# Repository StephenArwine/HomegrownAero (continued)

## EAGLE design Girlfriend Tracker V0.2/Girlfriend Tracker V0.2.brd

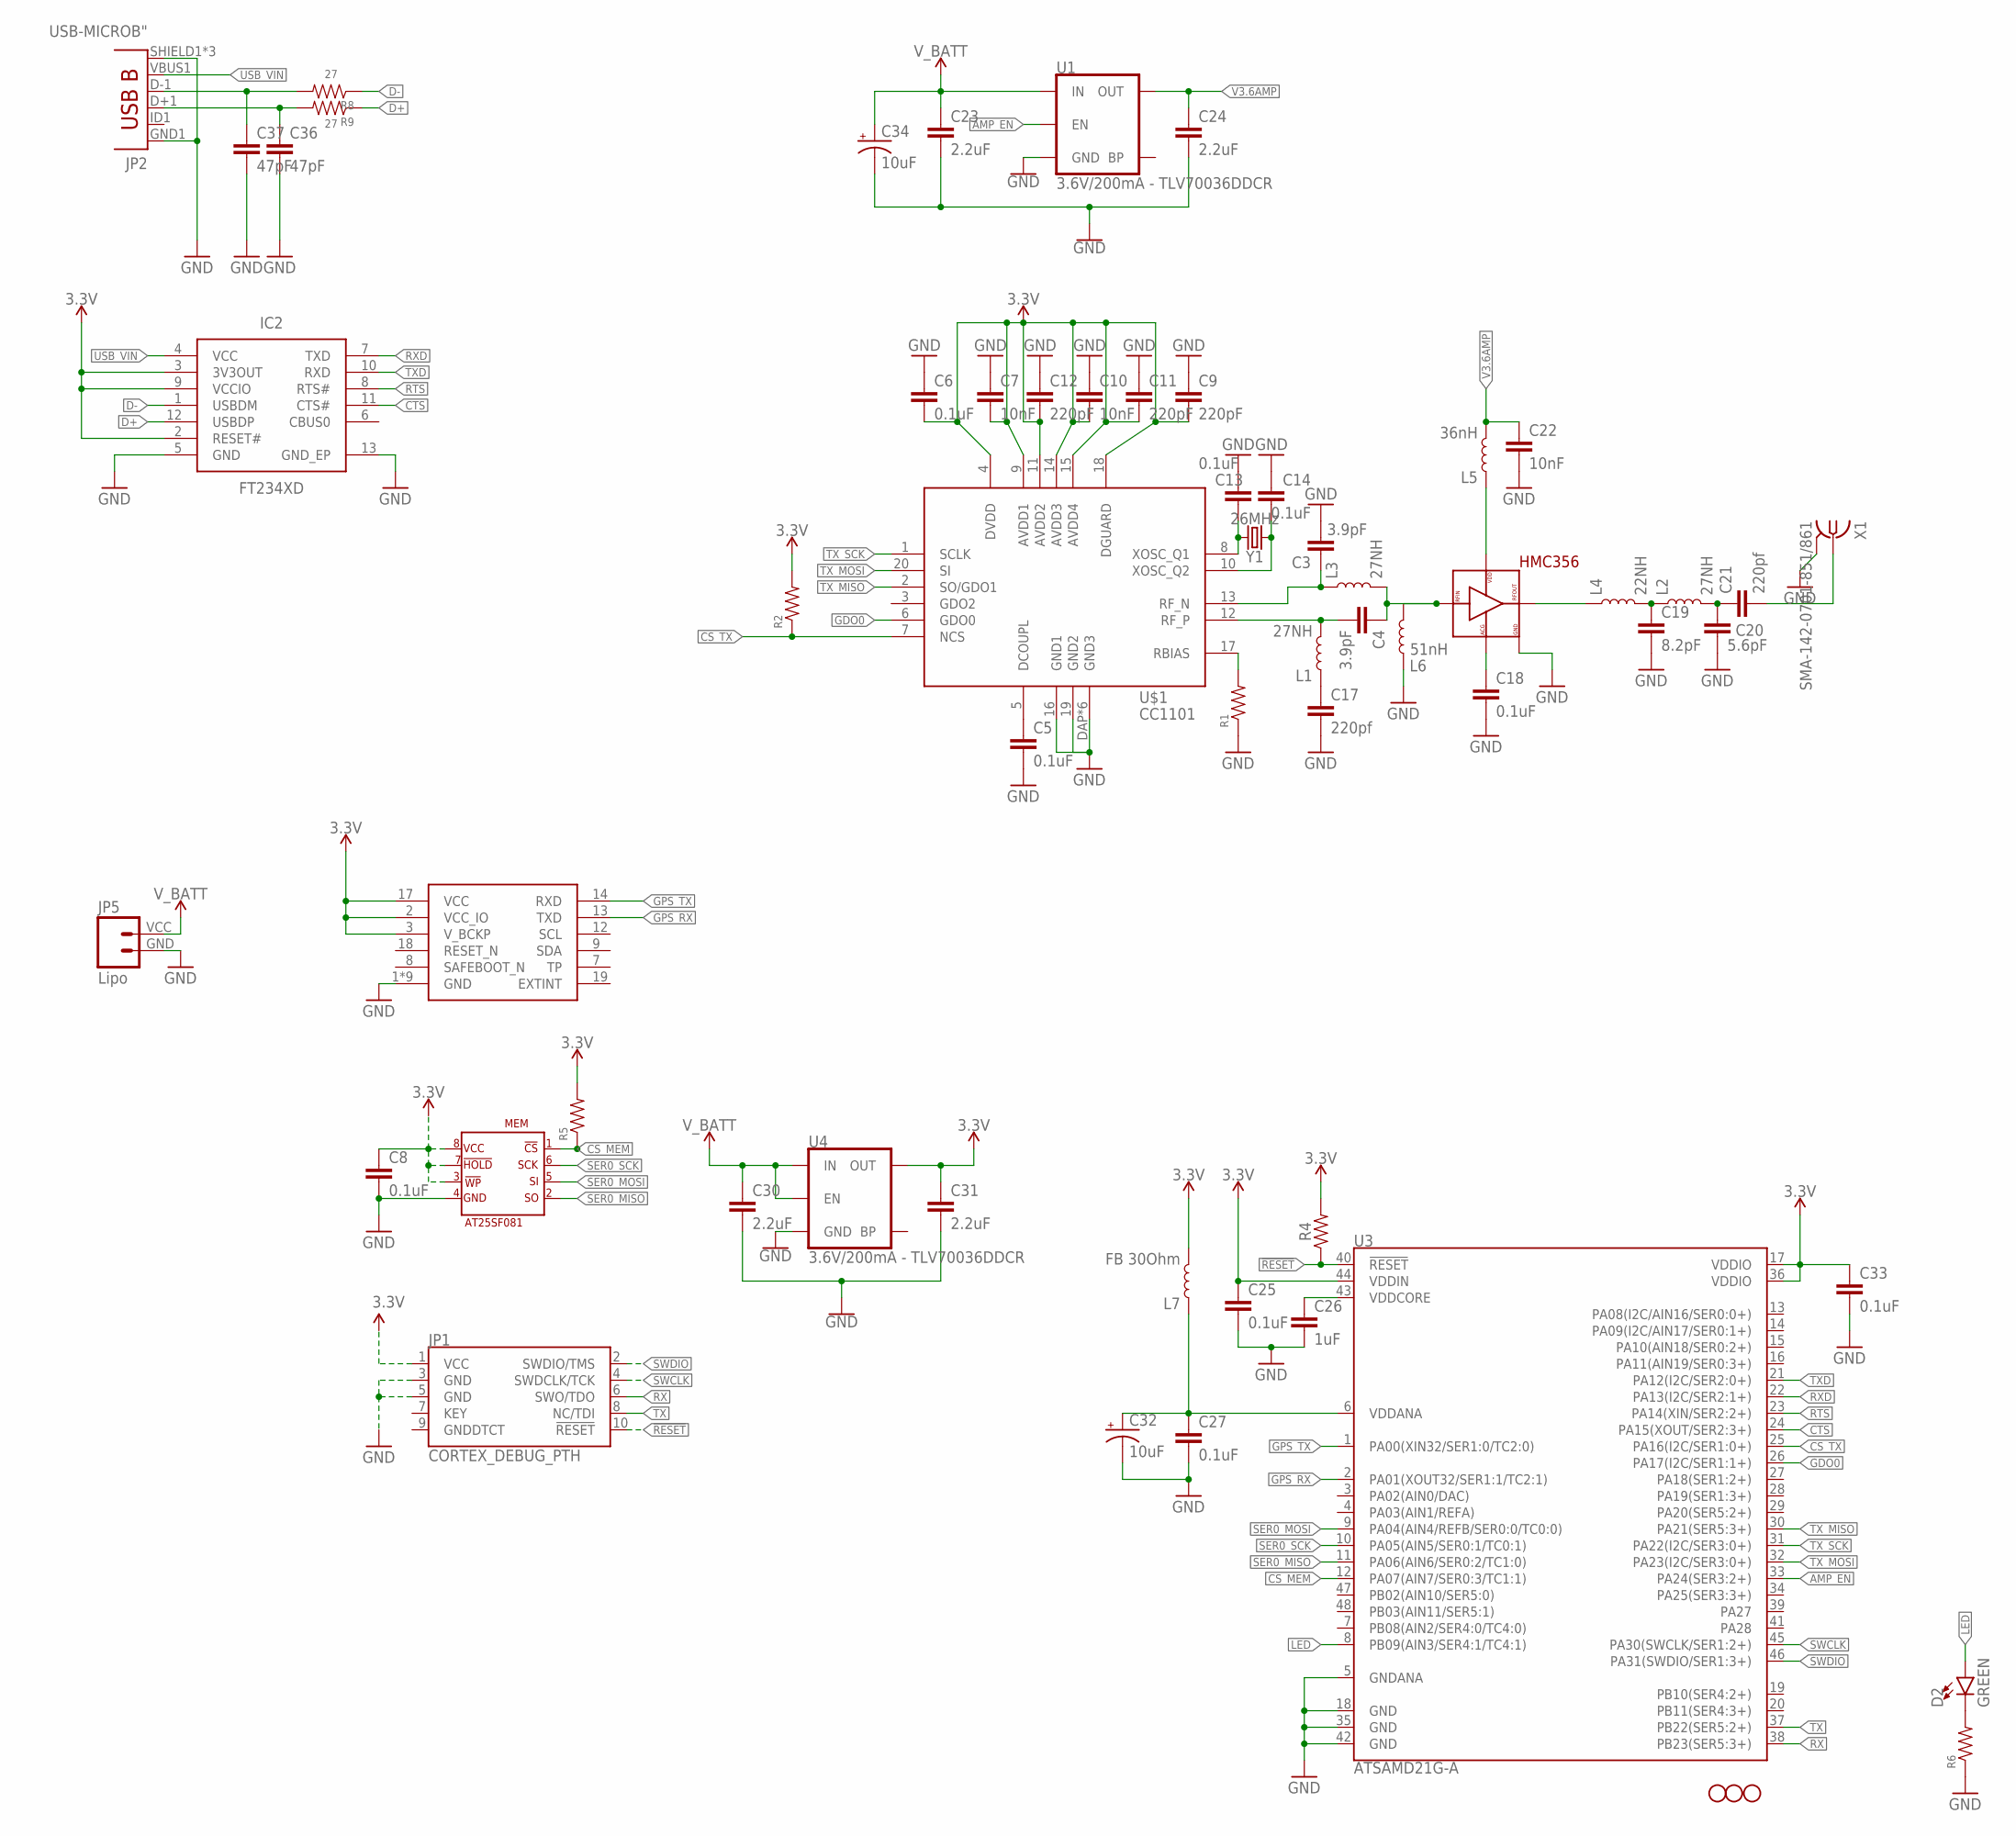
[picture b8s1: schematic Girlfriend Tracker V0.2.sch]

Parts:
C3, C4: 3.9pF; 0402
C5, C6, C8, C13, C14, C18, C25, C27, C33: 0.1uF; 0402
C7, C10, C22: 10nF; 0402
C9, C11, C12: 220pF; 0402
C17, C21: 220pf; 0402
C19: 8.2pF; 0402
C20: 5.6pF; 0402
C23, C24, C30, C31: 2.2uF; 0603
C26: 1uF; 0402
C32, C34: 10uF; EIA3216
C36, C37: 47pF; 0402
D2: GREEN; LED-1206
H1, H2, H3: STAND-OFFTIGHT; STAND-OFF-TIGHT
IC1: SAM-M8Q
IC2: FT234XD; SON45P300X300X80-13N
JP1: CORTEX_DEBUG_PTH; 2X5-PTH-1.27MM
JP2: USB-MICROB"; USB-B-MICRO-SMD_V03
JP5: Lipo; JST-2-SMD-VERT
L1, L2, L3: 27NH; 0402
L4: 22NH; 0402
L5: 36nH; 0402
L6: 51nH; 0402
L7: FB 30Ohm; 0603
MEM: AT25SF081
R1, R2, R4, R5, R6: 0402
R8, R9: 27; 0402
U1, U4: 3.6V/200mA - TLV70036DDCR; SOT23-5
U3: ATSAMD21G-A; TQFP-48
U$1: CC1101
U$3: HMC356; QFN16_HMC356
X1: SMA-142-0701-851/861; J502-ND-142-0701-851/861
Y1: 26MHz; CRYSTAL-SMD-3.2X2.5MM

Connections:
3.3V: C6.2, C7.2, C8.1, C9.2, C10.2, C11.2, C12.2, C25.1, C31.1, C33.1, IC1.2 (VCC_IO), IC1.3 (V_BCKP), IC1.17 (VCC), IC2.2 (RESET#), IC2.3 (3V3OUT), IC2.9 (VCCIO), JP1.1 (VCC), L7.2, MEM.!HOLD, MEM.!WP, MEM.VCC, R2.2, R4.2, R5.2, U3.17 (VDDIO), U3.36 (VDDIO), U3.44 (VDDIN), U4.5 (OUT), U$1.4 (DVDD), U$1.9 (AVDD1), U$1.11 (AVDD2), U$1.14 (AVDD3), U$1.15 (AVDD4), U$1.18 (DGUARD)
!RESET: JP1.10 (!RESET), R4.1, U3.40 (!RESET!)
AMP_EN: U1.3 (EN), U3.33 (PA24(SER3:2+))
CS_MEM: MEM.!CS, R5.1, U3.12 (PA07(AIN7/SER0:3/TC1:1))
CS_TX: R2.1, U3.25 (PA16(I2C/SER1:0+)), U$1.7 (NCS)
CTS: IC2.11 (CTS#), U3.24 (PA15(XOUT/SER2:3+))
D+: IC2.12 (USBDP), R9.1
D-: IC2.1 (USBDM), R8.1
GDO0: U3.26 (PA17(I2C/SER1:1+)), U$1.6 (GDO0)
GND: C3.2, C5.2, C6.1, C7.1, C8.2, C9.1, C10.1, C11.1, C12.1, C13.1, C14.2, C17.2, C18.2, C19.2, C20.2, C22.2, C23.2, C24.2, C25.2, C26.2, C27.2, C30.2, C31.2, C32.C (-), C33.2, C34.C (-), C36.2, C37.2, IC1.1 (GND), IC1.4 (GND), IC1.5 (GND), IC1.6 (GND), IC1.10 (GND), IC1.11 (GND), IC1.15 (GND), IC1.16 (GND), IC1.20 (GND), IC2.5 (GND), IC2.13 (GND_EP), JP1.3 (GND), JP1.5 (GND), JP2.GND1 (GND), JP2.SHIELD1 (SHIELD), JP2.SHIELD2 (SHIELD), JP2.SHIELD3 (SHIELD), JP5.GND (1), L6.1, MEM.GND, R1.1, R6.1, U1.2 (GND), U3.5 (GNDANA), U3.18 (GND), U3.35 (GND), U3.42 (GND), U4.2 (GND), U$1.16 (GND1), U$1.19 (GND2), U$1.DAP (GND3), U$1.P$1 (GND3), U$1.P$2 (GND3), U$1.P$3 (GND3), U$1.P$4 (GND3), U$1.P$5 (GND3), U$3.P$2, U$3.P$4, U$3.P$6, U$3.P$16, U$3.P$17, U$3.P$17_1, U$3.P$17_2, U$3.P$17_3, U$3.P$17_4, X1.G@1 (2), X1.G@2 (2), X1.G@3 (2), X1.G@4 (2)
GPS_RX: IC1.13 (TXD), U3.2 (PA01(XOUT32/SER1:1/TC2:1))
GPS_TX: IC1.14 (RXD), U3.1 (PA00(XIN32/SER1:0/TC2:0))
LED: D2.A, U3.8 (PB09(AIN3/SER4:1/TC4:1))
unnamed: C17.1, L1.1
unnamed: C36.1, JP2.D+1 (D+), R9.2
unnamed: C19.1, L2.1, L4.2
unnamed: C13.2, U$1.8 (XOSC_Q1), Y1.3 (2)
unnamed: C20.1, C21.1, L2.2
unnamed: C5.1, U$1.5 (DCOUPL)
unnamed: R1.2, U$1.17 (RBIAS)
unnamed: C18.1, U$3.P$7
unnamed: C21.2, X1.1
unnamed: L5.1, U$3.P$15
unnamed: C4.1, L3.2, L6.2, U$3.P$3
unnamed: C26.1, U3.43 (VDDCORE)
unnamed: C27.1, C32.A (+), L7.1, U3.6 (VDDANA)
unnamed: L4.1, U$3.P$11
unnamed: C37.1, JP2.D-1 (D-), R8.2
unnamed: C14.1, U$1.10 (XOSC_Q2), Y1.1
unnamed: D2.C, R6.2
RF_N: C3.1, L3.1, U$1.13 (RF_N)
RF_P: C4.2, L1.2, U$1.12 (RF_P)
RTS: IC2.8 (RTS#), U3.23 (PA14(XIN/SER2:2+))
RX: JP1.6 (SWO/TDO), U3.38 (PB23(SER5:3+))
RXD: IC2.7 (TXD), U3.22 (PA13(I2C/SER2:1+))
SER0_MISO: MEM.SO, U3.11 (PA06(AIN6/SER0:2/TC1:0))
SER0_MOSI: MEM.SI, U3.9 (PA04(AIN4/REFB/SER0:0/TC0:0))
SER0_SCK: MEM.SCK, U3.10 (PA05(AIN5/SER0:1/TC0:1))
SWCLK: JP1.4 (SWDCLK/TCK), U3.45 (PA30(SWCLK/SER1:2+))
SWDIO: JP1.2 (SWDIO/TMS), U3.46 (PA31(SWDIO/SER1:3+))
TX: JP1.8 (NC/TDI), U3.37 (PB22(SER5:2+))
TXD: IC2.10 (RXD), U3.21 (PA12(I2C/SER2:0+))
TX_MISO: U3.30 (PA21(SER5:3+)), U$1.2 (SO/GDO1)
TX_MOSI: U3.32 (PA23(I2C/SER3:0+)), U$1.20 (SI)
TX_SCK: U3.31 (PA22(I2C/SER3:0+)), U$1.1 (SCLK)
USB_VIN: IC2.4 (VCC), JP2.VBUS1 (VBUS)
V3.6AMP: C22.1, C24.1, L5.2, U1.5 (OUT)
V_BATT: C23.1, C30.1, C34.A (+), JP5.VCC (2), U1.1 (IN), U4.1 (IN), U4.3 (EN)

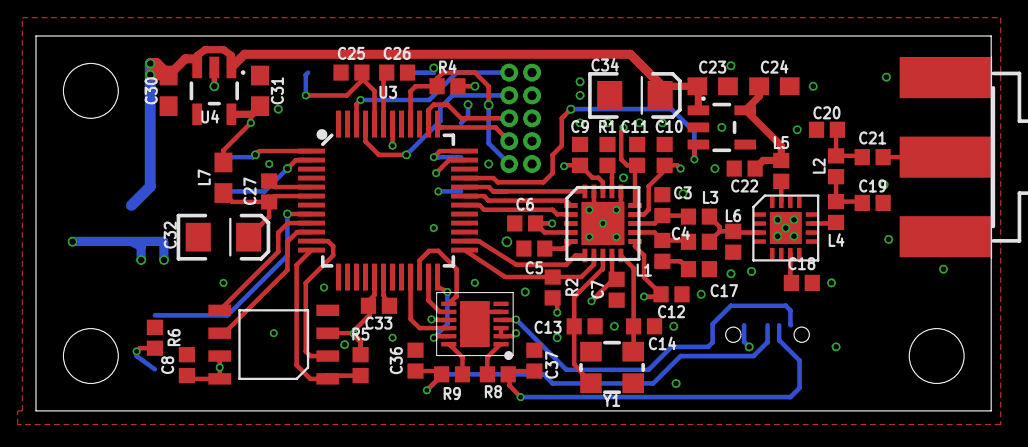
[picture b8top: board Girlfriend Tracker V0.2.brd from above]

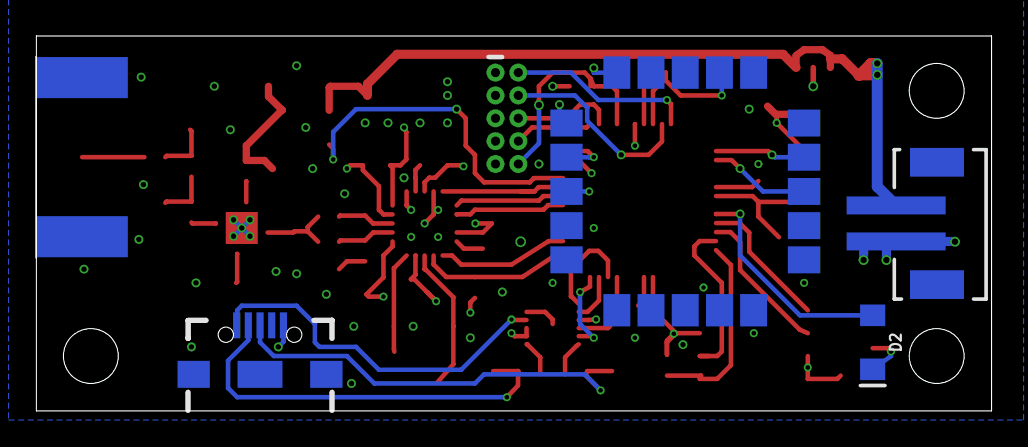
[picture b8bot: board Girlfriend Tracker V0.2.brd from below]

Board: 4 copper layers, 53.1 x 20.8 mm, 61 parts (5 on the bottom side), 48 nets.

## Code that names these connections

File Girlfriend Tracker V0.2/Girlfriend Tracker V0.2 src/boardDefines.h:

//#include <util.h>

#define  USART0 0
#define  USART1 1



//Track'em V0.1



//const static Pin cs_mem = {.group = 0, .pin = 2};
const static Pin cs_tx = {.group = 0, .pin = 16};
const static Pin Pin_GDO0 = {.group = 0, .pin = 17};
	
const static Pin AMP_EN = {.group = 0, .pin = 24}; 



const static Pin GPSTxPo = {.group = 0, .pin = 0, .mux = MUX_PA00D_SERCOM1_PAD0};
const static Pin GPSRxPo = {.group = 0, .pin = 1, .mux = MUX_PA01D_SERCOM1_PAD1};

//const static Pin ComRxPo = {.group = 0, .pin = 25, .mux = MUX_PA25C_SERCOM1_PAD3};
//const static Pin ComTxPo = {.group = 0, .pin = 24, .mux = MUX_PA24C_SERCOM1_PAD2};

const static Pin LEDPin = {.group = 1, .pin = 9};

const static Pin spiMOSI = {.group = 0, .pin = 23, .mux = MUX_PA23D_SERCOM5_PAD1};
const static Pin spiMISO = {.group = 0, .pin = 21, .mux = MUX_PA21C_SERCOM5_PAD3};
const static Pin spiSCK = {.group = 0, .pin = 22, .mux = MUX_PA22D_SERCOM5_PAD0};

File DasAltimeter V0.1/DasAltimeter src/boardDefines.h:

//#include <util.h>

#define SPI0 0
#define SPI1 1
#define SPI2 2
#define  USART3 3


//dasAltimeter


bool writeLog;

const static Pin cs_mem = {.group = 0, .pin = 18};
const static Pin cs_baro = {.group = 0, .pin = 15};
const static Pin cs_gyro = {.group = 0, .pin = 10};
const static Pin cs_accel = {.group = 1, .pin = 10};

const static Pin TxPo = {.group = 0, .pin = 22, .mux = MUX_PA22C_SERCOM3_PAD0};
const static Pin RxPo = {.group = 0, .pin = 23, .mux = MUX_PA23C_SERCOM3_PAD1};

const static Pin spi0MOSI = {.group = 0, .pin = 8, .mux = MUX_PA08C_SERCOM0_PAD0};
const static Pin spi0MISO = {.group = 0, .pin = 11, .mux = MUX_PA11C_SERCOM0_PAD3};
const static Pin spi0SCK = {.group = 0, .pin = 9, .mux = MUX_PA09C_SERCOM0_PAD1};

const static Pin spi1MOSI = {.group = 0, .pin = 16, .mux = MUX_PA16C_SERCOM1_PAD0};
const static Pin spi1MISO = {.group = 0, .pin = 19, .mux = MUX_PA19C_SERCOM1_PAD3};
const static Pin spi1SCK = {.group = 0, .pin = 17, .mux = MUX_PA17C_SERCOM1_PAD1};

const static Pin spi2MOSI = {.group = 0, .pin = 12, .mux = MUX_PA12C_SERCOM2_PAD0};
const static Pin spi2MISO = {.group = 0, .pin = 13, .mux = MUX_PA13C_SERCOM2_PAD1};
const static Pin spi2SCK = {.group = 0, .pin = 14, .mux = MUX_PA14C_SERCOM2_PAD2};

const static Pin LedPin = {.group = 0, .pin = 20};
const static Pin buzzerPin = {.group = 0, .pin = 21, .cfg = 0x40};
const static Pin senseBatPin = {.group = 0, .pin = 6, .chan = 6};

const static Pin senseAPin = {.group = 1, .pin = 3, .mux = 1, .chan = 11};
const static Pin fireAPin = {.group = 1, .pin = 23};

const static Pin senseBPin = {.group = 1, .pin = 2, .mux = 1, .chan = 10};
const static Pin fireBPin = {.group = 1, .pin = 22};

const static Pin senseCPin = {.group = 0, .pin = 3, .chan = 1};
const static Pin fireCPin = {.group = 0, .pin = 25};

const static Pin senseDPin = {.group = 0, .pin = 2, .chan = 0};
const static Pin fireDPin = {.group = 0, .pin = 24};

const static Pin analogAccelPin = {.group = 0, .pin = 7, .chan = 7};


#define FLIGHTZEROSTART 0x100
#define FLIGHTZEROEND 0x103

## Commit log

2017-08-23 Rename Util.h to util.h
2017-08-28 Create bitBang
2017-08-28 Rename bitBang to bitBang.c
2017-08-29 home stuff
2017-08-31 usart inputed but not working
2017-09-03 changes are good right
2017-10-02 doesnt matter, scrap
2017-10-03 building altimeter
2017-10-05 dasAltimeter
2017-10-06 working on getting SPI to work, got a ways to go
2017-10-06 none
2017-10-07 10/5 push
2017-10-07 created bigBang
2017-10-08 set up flight
2017-10-09 getting sensors input, no real work
2017-10-11 SPI is pretty much working, dma is useless due to being much slower than CS
2017-10-12 10/11 push, spi is pretty
2017-10-13 Dont know why but SPI is now happy and works great... great...
2017-10-14 got spi working on test board( baro only)
2017-10-14 minor v1.1 borad changes
2017-10-14 measuring altitude
2017-10-15 working on sample libary and IMU
2017-10-16 doing some accell work
2017-10-19 correct G offset found
2017-10-20 sample now does accel and baro
    sample now does accel and baro
2017-10-21 day one changes
2017-10-21 Analog accel tuned
2017-10-22 dasaltimeter 1.1 board work
2017-10-22 changes to eagle stuff
2017-10-22 DasAltimeter V0.1 board layout done
2017-10-23 V0.1 board
2017-10-23 DasAltimeter V0.1 sent to fab
2017-10-28 tuning
2017-11-07 setting up software
2017-11-11 digi accel finally working...
2017-11-11 rtc stuff?
2017-11-11 accelerometer setup in sample
2017-11-12 samples averaging and RTC set up
2017-11-12 tiny buzzer changes
2017-11-14 sample triggering timer works!
2017-11-16 setting up flight and TCC timers
2017-11-17 setting up usart
2017-11-17 fixed internal 32k osc startup stuff
2017-11-19 USART in and out working, sending sensor packet
2017-11-19 writing to mem, sample from mem
2017-11-20 adding matlab files
2017-11-21 no real changes, new comp side serial reciever
2017-11-21 from write smaple to write page
2017-11-27 beep start
2017-11-27 Update altimeter.h
    adding flash page buffer
2017-11-28 matlab things
2017-12-02 adding python stuff
2017-12-02 write 10 pages to memory
2017-12-03 lots of python work
2017-12-03 plotting stuff
2017-12-04 lots of python logging
2017-12-04 started on find flight
2017-12-05 broke data transfter, off by one error
2017-12-05 add page writing
2017-12-05 fix off by one (maybe)
2017-12-05 one buffer function
2017-12-06 fixed off by one errors, find flight end working! woohoo
2017-12-06 is flight logged function
2017-12-06 clean up flight search
2017-12-07 developed flight choice from python to device
2017-12-08 playing with mini altimeter idea
2017-12-09 flights are correctly? logging and chip erase
2017-12-10 breaking python :(
2017-12-10 maybe fixed test file
2017-12-10 fixed the python file
2017-12-11 kalman filter started
2017-12-12 Kalman filter baby!
2017-12-12 fixed plotting data
2017-12-13 not much
2017-12-14 logging is looking like it works 100%! woohoo
2017-12-15 cleaned up the days work
2017-12-15 Working on new tracker
2017-12-15 track'em updates
2017-12-16 Revert "playing with mini altimeter idea"
    This reverts commit 0304c3ccd9bbc4967d121740b09f5fd7c2a4b911.
2017-12-16 boards sent to fab
2017-12-16 this Track'em sent to fab
2017-12-17 adding velocity to the log
2017-12-17 minor python changes
2017-12-18 setup event type
2017-12-19 very little real progress...
2017-12-19 none test
2017-12-19 Rename kalmanGains.c to kalman.c
2017-12-19 Rename kalmanGains.h to kalman.h
2017-12-20 got rid of that ungodly wretched my_altimeter pointer and nothing blew up!
2017-12-21 fixed off by one error, something wrong with velocity
2018-01-05 vacation stuff
2018-01-06 new tracken program
2018-01-06 fix GPS for trackem v0.2
2018-01-07 tracking message parsed from GPS
2018-01-09 setting up CC1101 regs
2018-01-10 cc1101 regerster reading setup
2018-01-11 cc1101 config work
2018-01-12 getting close to transmitting i think
2018-01-12 minor changes to CC1101
2018-01-13 setting up trackem v0.2
2018-01-15 Girlfriend Tracker Ordered
2018-01-20 girlfriend tracker board updates
2018-01-20 tracker board work
2018-01-21 first work on altimeter V0.2
2018-01-23 python tuning
2018-01-23 includes
2018-01-24 fixed python twos comp error
2018-01-25 altimeter V0.3 sent to fab
2018-01-26 debugged work stuff
2018-01-26 created twos comp function
2018-01-26 minor settings.h fix
2018-01-27 moved page write location
2018-01-31 board changes
2018-02-01 post implamented
2018-02-03 pointing up done
2018-02-04 working on settings and igniter
2018-02-04 adding more flight numbers
2018-02-05 settings set up
2018-02-05 deployment settings reading/writing
2018-02-05 fixed sample tick time recording
2018-02-09 Das Altimeter V0.3 assembled and working!
2018-02-09 pyqt ex
2018-02-09 Altimeter V0.3 analog stuff tuned and working great at 16 bits
2018-02-11 added some error control
2018-02-15 before work
2018-02-16 buzzer startish
2018-02-18 before work 2
2018-02-18 tracker work
2018-02-21 square mock up
2018-03-02 montana stuff
2018-03-17 tring to to tracker test
2018-04-17 pre flight samples and v0.35
2018-04-22 first test flight!
2018-04-23 first flight data, set to detect launch and kalmen including accel
2018-04-23 flight one
2018-04-28 pictures
2018-04-28 updates to log size, including raw altitude and accelX
2018-04-28 a bunch of tuning for pointing up and accel data
2018-04-29 ready for test flight 2
2018-05-03 second flight log
2018-05-08 secondary kalman for baro only
2018-05-13 test flight three
2018-05-13 flight 3 and 4 data
2018-05-14 set up main deploy flight logic
2018-05-18 tracking stuff
2018-05-20 ready for ejection flight
2018-05-21 flgiht and tests
2018-09-30 setting up ignighter tests
2020-01-14 routed dasAltimeter V0.40 and updates to code
2020-01-15 send dasaltimeter v0.41 to fab
2020-12-21 ParaBeep V0.1 Ordered
2021-02-04 lots of parabeep code updates, gps started
2021-02-07 started working on parabeep V0.2 design
2021-02-12 parabeep v0.2 ordered
2021-02-12 parabeep v0.2 order third try
2021-02-24 working on parabeep v0.2, accel not working yet
2021-03-03 Parabeep V0.25 sent to fab
2021-03-15 bluetooth working, neeed usb c
2021-03-22 bluetooth working, usb next
2021-03-27 ParaBeep moved
2021-03-28 moved stuff around
2022-10-14 Adding tarfile member sanitization to extractall()
